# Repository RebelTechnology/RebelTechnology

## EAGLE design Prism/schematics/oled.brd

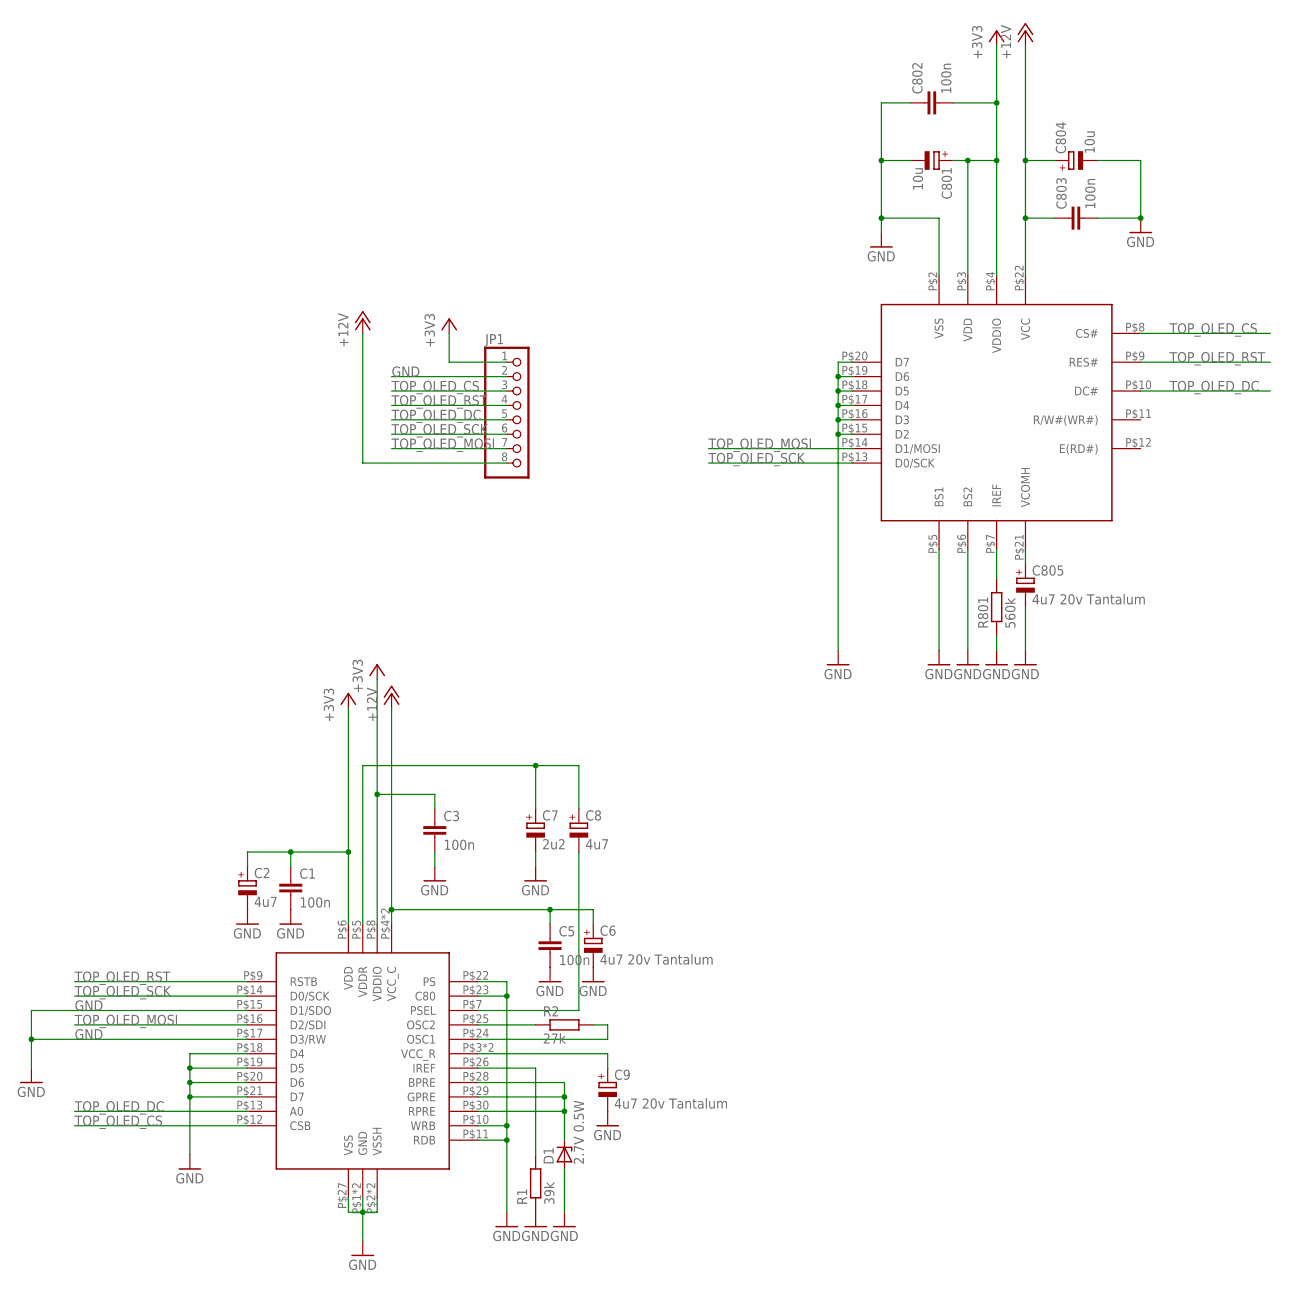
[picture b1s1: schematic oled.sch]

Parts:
C1, C3, C5, C802, C803: 100n; C0603
C2, C8: 4u7; CPOL-5
C6, C9, C805: 4u7 20v Tantalum; CT3216
C7: 2u2; CPOL-5
C801, C804: 10u; CPOL-5
D1: 2.7V 0.5W; SOD80C
JP1: PINHD-1X8; 1X08
OLED: MCOT096064AZ-RGBM
R1: 39k; 0603
R2: 27k; 0603
R801: 560k; 0603
U$1: MCOT096096AY

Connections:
+3V3: C1.1, C2.+, C3.1, C801.+, C802.2, JP1.1, OLED.P$3 (VDD), OLED.P$4 (VDDIO), U$1.P$6 (VDD), U$1.P$8 (VDDIO)
+12V: C5.1, C6.+, C803.1, C804.+, JP1.8, OLED.P$22 (VCC), U$1.P$4 (VCC_C), U$1.P$31 (VCC_C)
GND: C1.2, C2.-, C3.2, C5.2, C6.-, C7.-, C9.-, C801.-, C802.1, C803.2, C804.-, C805.-, D1.A, JP1.2, OLED.P$2 (VSS), OLED.P$5 (BS1), OLED.P$6 (BS2), OLED.P$15 (D2), OLED.P$16 (D3), OLED.P$17 (D4), OLED.P$18 (D5), OLED.P$19 (D6), OLED.P$20 (D7), R1.1, R801.1, U$1.P$1 (GND), U$1.P$2 (VSSH), U$1.P$10 (WRB), U$1.P$11 (RDB), U$1.P$15 (D1/SDO), U$1.P$17 (D3/RW), U$1.P$18 (D4), U$1.P$19 (D5), U$1.P$20 (D6), U$1.P$21 (D7), U$1.P$22 (PS), U$1.P$23 (C80), U$1.P$27 (VSS), U$1.P$33 (VSSH), U$1.P$34 (GND)
unnamed: C9.+, U$1.P$3 (VCC_R), U$1.P$32 (VCC_R)
unnamed: C7.+, C8.+, U$1.P$5 (VDDR)
unnamed: C805.+, OLED.P$21 (VCOMH)
unnamed: C8.-, U$1.P$7 (PSEL)
unnamed: OLED.P$7 (IREF), R801.2
unnamed: D1.C, U$1.P$28 (BPRE), U$1.P$29 (GPRE), U$1.P$30 (RPRE)
unnamed: R2.1, U$1.P$25 (OSC2)
unnamed: R2.2, U$1.P$24 (OSC1)
unnamed: R1.2, U$1.P$26 (IREF)
TOP_OLED_CS: JP1.3, OLED.P$8 (CS#), U$1.P$12 (CSB)
TOP_OLED_DC: JP1.5, OLED.P$10 (DC#), U$1.P$13 (A0)
TOP_OLED_MOSI: JP1.7, OLED.P$14 (D1/MOSI), U$1.P$16 (D2/SDI)
TOP_OLED_RST: JP1.4, OLED.P$9 (RES#), U$1.P$9 (RSTB)
TOP_OLED_SCK: JP1.6, OLED.P$13 (D0/SCK), U$1.P$14 (D0/SCK)

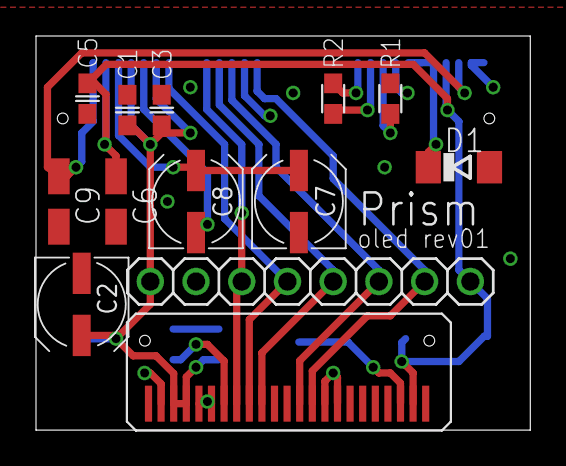
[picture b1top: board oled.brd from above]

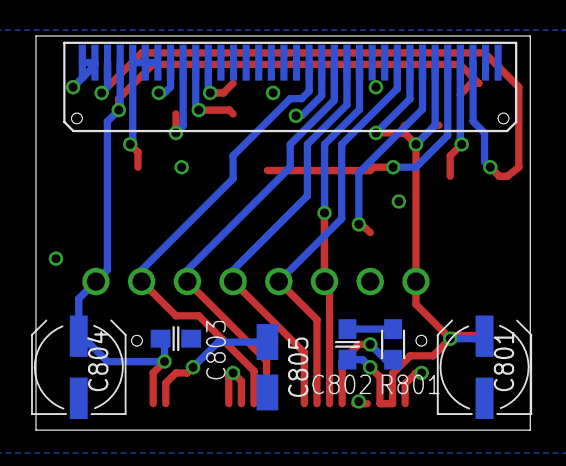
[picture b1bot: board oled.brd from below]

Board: 2 copper layers, 27.5 x 21.9 mm, 20 parts (7 on the bottom side), 17 nets.

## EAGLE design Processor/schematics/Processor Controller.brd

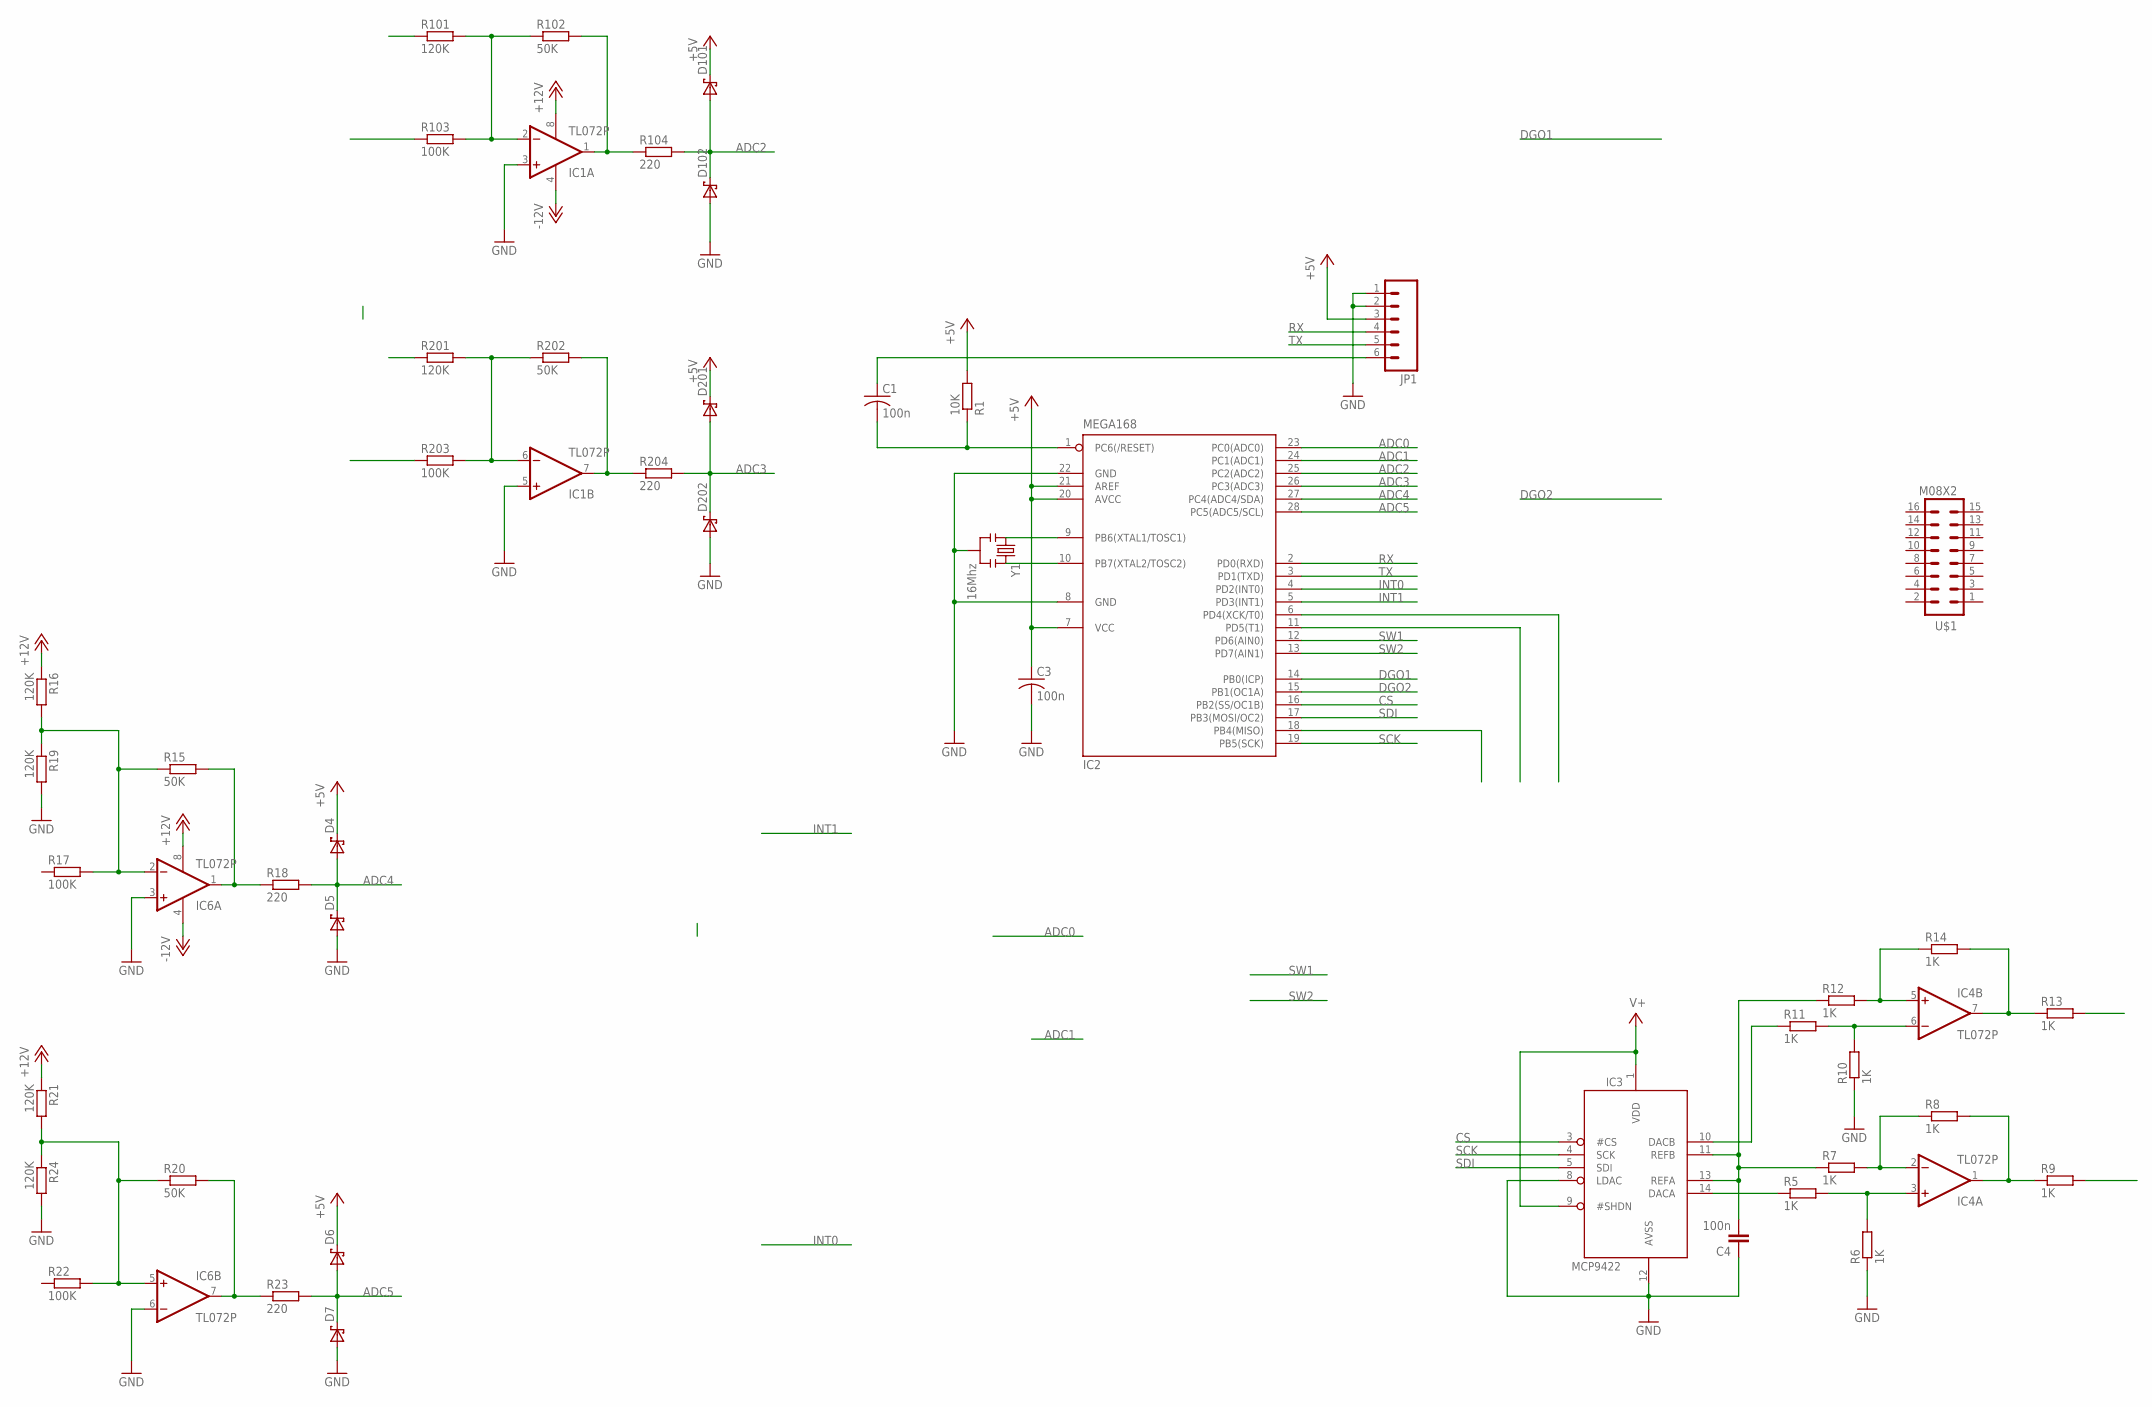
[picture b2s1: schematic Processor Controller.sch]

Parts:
C1, C3: 100n; C050-024X044
C4: 100n; C050-030X075
D4, D5, D6, D7, D101, D102, D201, D202: DS_E2L; E2LINE
IC1, IC4, IC6: TL072P; DIL08
IC2: MEGA168; DIL28-3
IC3: MCP9422; DIL14
JP1: M06SIP; 1X06
R1: 10K; 0204/7
R5, R6, R7, R8, R9, R10, R11, R12, R13, R14: 1K; 0204/7
R15, R20, R102, R202: 50K; 0204/7
R16, R19, R21, R24, R101, R201: 120K; 0204/7
R17, R22, R103, R203: 100K; 0204/7
R18, R23, R104, R204: 220; 0204/7
U$1: M08X2; 2X8
Y1: 16Mhz; RESONATOR-PTH

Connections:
+5V: C3.1, D4.1 (K), D6.1 (K), D101.1 (K), D201.1 (K), IC2.7 (VCC), IC2.20 (AVCC), IC2.21 (AREF), JP1.3, R1.2
+12V: IC1.8 (V+), IC6.8 (V+), R16.1, R21.1
-12V: IC1.4 (V-), IC6.4 (V-)
ADC0: IC2.23 (PC0(ADC0))
ADC1: IC2.24 (PC1(ADC1))
ADC2: D101.2 (A), D102.1 (K), IC2.25 (PC2(ADC2)), R104.2
ADC3: D201.2 (A), D202.1 (K), IC2.26 (PC3(ADC3)), R204.2
ADC4: D4.2 (A), D5.1 (K), IC2.27 (PC4(ADC4/SDA)), R18.2
ADC5: D6.2 (A), D7.1 (K), IC2.28 (PC5(ADC5/SCL)), R23.2
ALTA: IC2.11 (PD5(T1))
CS: IC2.16 (PB2(SS/OC1B)), IC3.3 (#CS)
DGO1: IC2.14 (PB0(ICP))
DGO2: IC2.15 (PB1(OC1A))
GND: C3.2, C4.1, D5.2 (A), D7.2 (A), D102.2 (A), D202.2 (A), IC1.3 (+IN), IC1.5 (+IN), IC2.8 (GND), IC2.22 (GND), IC3.8 (LDAC), IC3.12 (AVSS), IC6.3 (+IN), IC6.6 (-IN), JP1.1, JP1.2, R6.1, R10.1, R19.2, R24.2, Y1.2
INT0: IC2.4 (PD2(INT0))
INT1: IC2.5 (PD3(INT1))
unnamed: IC1.2 (-IN), R101.2, R102.1, R103.2
unnamed: IC1.1 (OUT), R102.2, R104.1
unnamed: IC1.6 (-IN), R201.2, R202.1, R203.2
unnamed: IC1.7 (OUT), R202.2, R204.1
unnamed: C4.2, IC3.11 (REFB), IC3.13 (REFA), R7.1, R12.1
unnamed: IC4.2 (-IN), R7.2, R8.1
unnamed: IC4.3 (+IN), R5.2, R6.2
unnamed: IC3.14 (DACA), R5.1
unnamed: IC4.1 (OUT), R8.2, R9.1
unnamed: IC2.9 (PB6(XTAL1/TOSC1)), Y1.1
unnamed: IC2.10 (PB7(XTAL2/TOSC2)), Y1.3
unnamed: IC6.2 (-IN), R15.1, R16.2, R17.2, R19.1
unnamed: C1.1, JP1.6
unnamed: IC3.10 (DACB), R11.1
unnamed: IC4.6 (-IN), R10.2, R11.2
unnamed: IC4.5 (+IN), R12.2, R14.1
unnamed: C1.2, IC2.1 (PC6(/RESET)), R1.1
unnamed: IC4.7 (OUT), R13.1, R14.2
unnamed: IC6.1 (OUT), R15.2, R18.1
unnamed: IC6.7 (OUT), R20.2, R23.1
unnamed: IC6.5 (+IN), R20.1, R21.2, R22.2, R24.1
RX: IC2.2 (PD0(RXD)), JP1.4
SCK: IC2.19 (PB5(SCK)), IC3.4 (SCK)
SDI: IC2.17 (PB3(MOSI/OC2)), IC3.5 (SDI)
SW1: IC2.12 (PD6(AIN0))
SW2: IC2.13 (PD7(AIN1))
TRIGA: IC2.6 (PD4(XCK/T0))
TX: IC2.3 (PD1(TXD)), JP1.5
V+: IC3.1 (VDD), IC3.9 (#SHDN), IC4.8 (V+)
V-: IC4.4 (V-)

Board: 2 copper layers, 48 parts (0 on the bottom side), 35 nets, no tracks yet.

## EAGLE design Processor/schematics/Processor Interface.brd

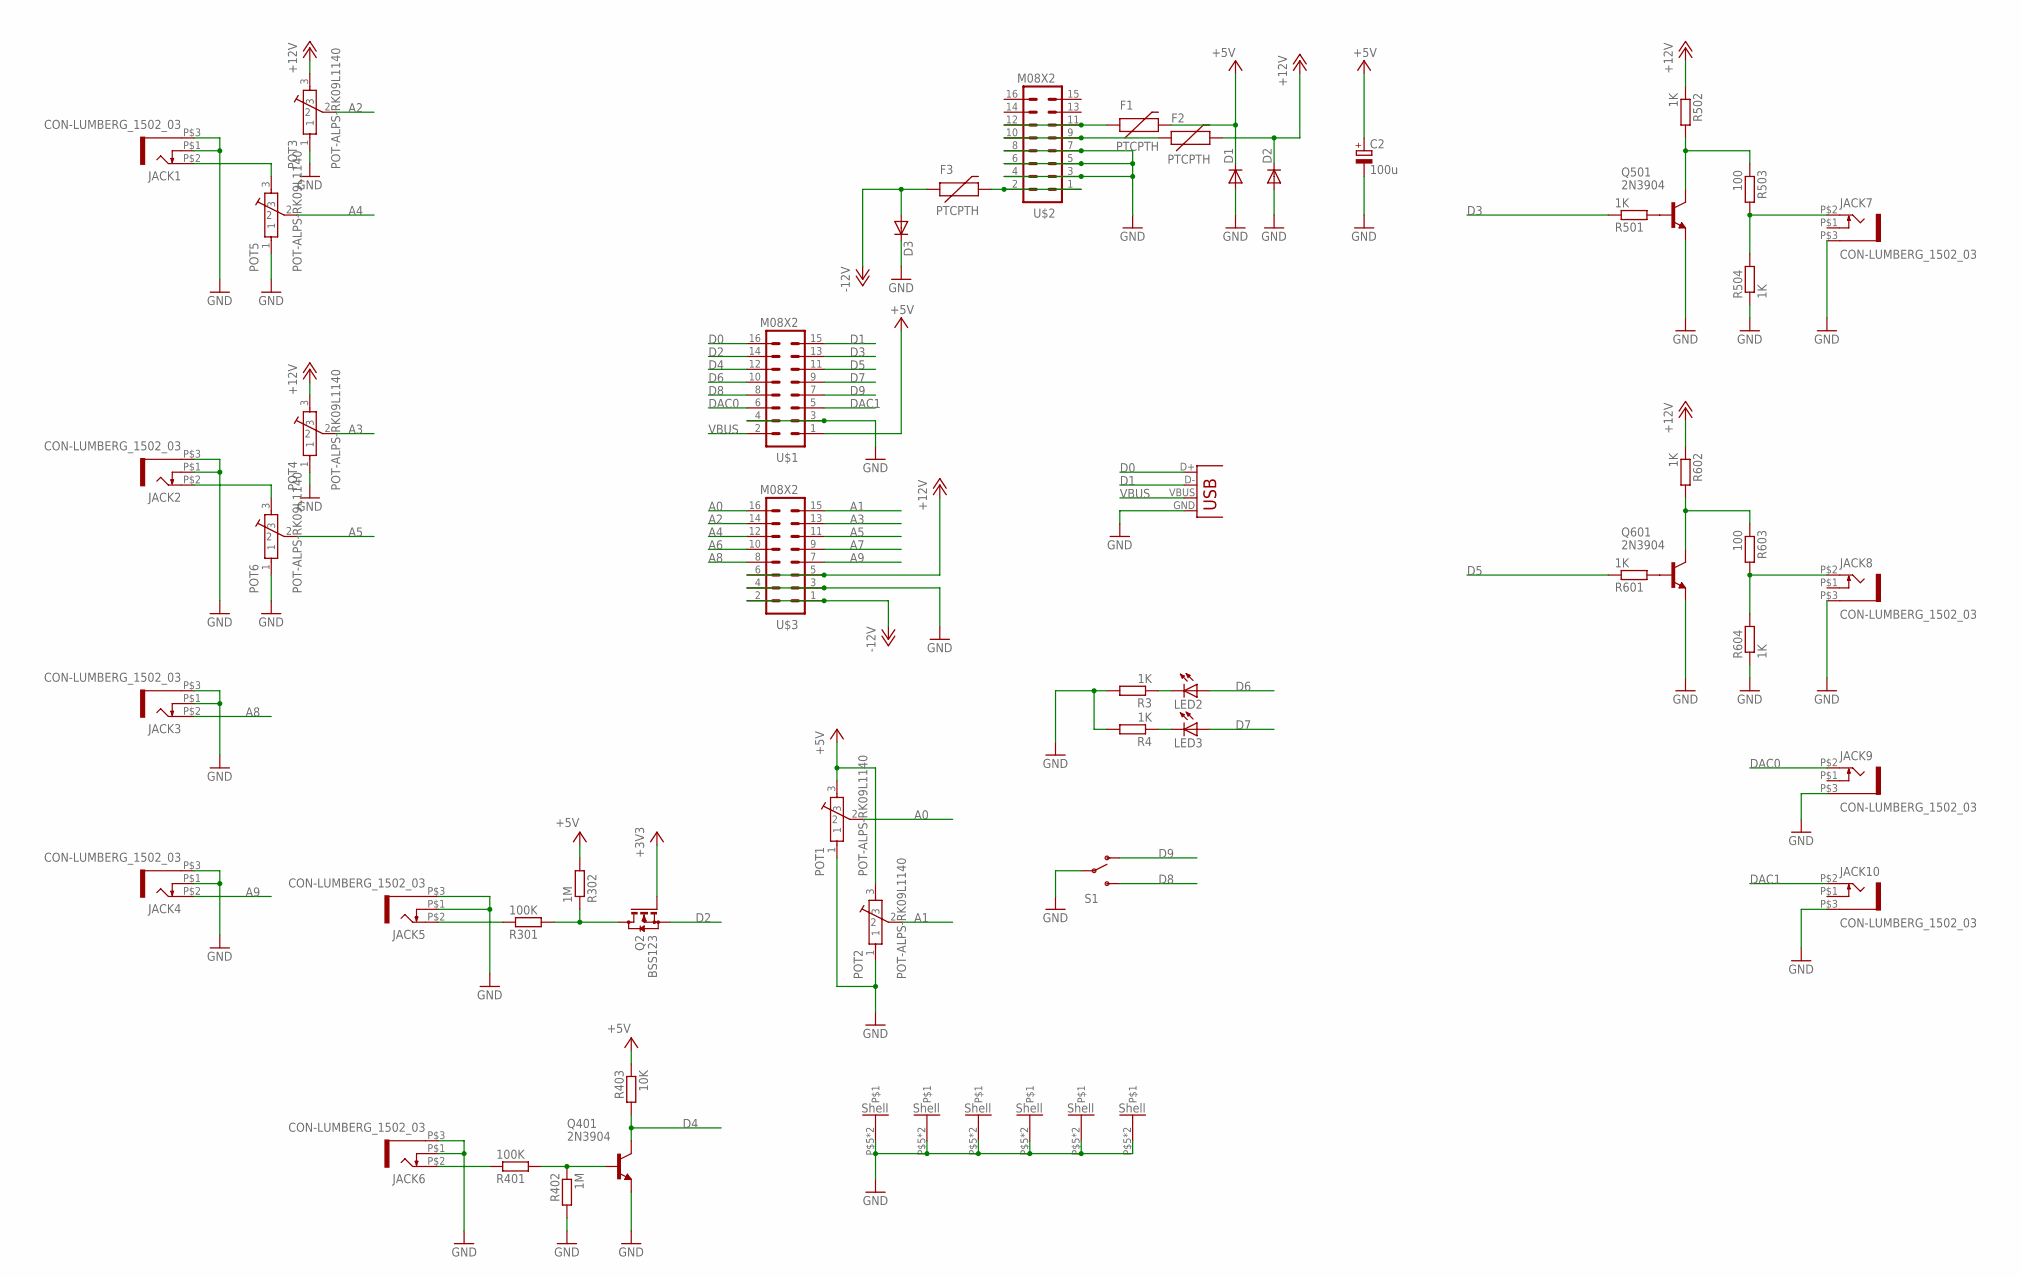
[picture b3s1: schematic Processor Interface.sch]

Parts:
C2: 100u; E5-6
D1, D2, D3: DIODEPTH; DIODE-1N4001
F1, F2, F3: PTCPTH; PTC
JACK1, JACK2, JACK3, JACK4, JACK5, JACK6, JACK7, JACK8, JACK9, JACK10: CON-LUMBERG_1502_03
LED2, LED3: LED3MM
POT1, POT2, POT3, POT4, POT5, POT6: POT-ALPS-RK09L1140
Q2: BSS123; SOT23
Q401, Q501, Q601: 2N3904; TO92
R3, R4, R501, R502, R504, R601, R602, R604: 1K; 0204/7
R301, R401: 100K; 0204/7
R302, R402: 1M; 0204/7
R403: 10K; 0204/7
R503, R603: 100; 0204/7
S1: SWITCH-SPST; SWITCH-SPDT-SALECOM-T8014
U$1, U$2, U$3: M08X2; 2X8
X1: USBPTH-VERTICAL; USB-B-PTH-VERTICAL

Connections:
+3V3: Q2.1 (G)
+5V: C2.+, D1.C, F1.P$2 (2), POT1.3, POT2.3, R302.2, R403.1, U$1.1
+12V: D2.C, F2.P$2 (2), POT3.3, POT4.3, R502.1, R602.1, U$3.5, U$3.6
-12V: D3.A, F3.P$1 (1), U$3.1, U$3.2
A0: POT1.2, U$3.16
A1: POT2.2, U$3.15
A2: POT3.2, U$3.14
A3: POT4.2, U$3.13
A4: POT5.2, U$3.12
A5: POT6.2, U$3.11
A6: U$3.10
A7: U$3.9
A8: JACK3.P$2 (3), U$3.8
A9: JACK4.P$2 (3), U$3.7
D0: U$1.16, X1.D+
D1: U$1.15, X1.D-
D2: Q2.2 (S), U$1.14
D3: R501.1, U$1.13
D4: Q401.1 (C), R403.2, U$1.12
D5: R601.1, U$1.11
D6: LED2.A, U$1.10
D7: LED3.A, U$1.9
D8: S1.3 (S), U$1.8
D9: S1.1 (O), U$1.7
DAC0: JACK9.P$2 (3), U$1.6
DAC1: JACK10.P$2 (3), U$1.5
GND: C2.-, D1.A, D2.A, D3.C, JACK1.P$1 (4), JACK1.P$3 (5), JACK2.P$1 (4), JACK2.P$3 (5), JACK3.P$1 (4), JACK3.P$3 (5), JACK4.P$1 (4), JACK4.P$3 (5), JACK5.P$1 (4), JACK5.P$3 (5), JACK6.P$1 (4), JACK6.P$3 (5), JACK7.P$3 (5), JACK8.P$3 (5), JACK9.P$3 (5), JACK10.P$3 (5), POT1.1, POT1.P$5, POT1.P$6, POT2.1, POT2.P$5, POT2.P$6, POT3.1, POT3.P$5, POT3.P$6, POT4.1, POT4.P$5, POT4.P$6, POT5.1, POT5.P$5, POT5.P$6, POT6.1, POT6.P$5, POT6.P$6, Q401.3 (E), Q501.3 (E), Q601.3 (E), R3.2, R4.2, R402.2, R504.1, R604.1, S1.2, U$1.3, U$1.4, U$2.3, U$2.4, U$2.5, U$2.6, U$2.7, U$2.8, U$3.3, U$3.4, X1.GND
unnamed: JACK1.P$2 (3), POT5.3
unnamed: Q2.3 (D), R301.2, R302.1
unnamed: F3.P$2 (2), U$2.1, U$2.2
unnamed: JACK2.P$2 (3), POT6.3
unnamed: LED2.K (C), R3.1
unnamed: LED3.K (C), R4.1
unnamed: Q601.2 (B), R601.2
unnamed: JACK5.P$2 (3), R301.1
unnamed: JACK8.P$2 (3), R603.2, R604.2
unnamed: Q401.2 (B), R401.2, R402.1
unnamed: Q601.1 (C), R602.2, R603.1
unnamed: Q501.2 (B), R501.2
unnamed: JACK7.P$2 (3), R503.2, R504.2
unnamed: Q501.1 (C), R502.2, R503.1
unnamed: JACK6.P$2 (3), R401.1
unnamed: F1.P$1 (1), U$2.11, U$2.12
unnamed: F2.P$1 (1), U$2.9, U$2.10
VBUS: U$1.2, X1.VBUS

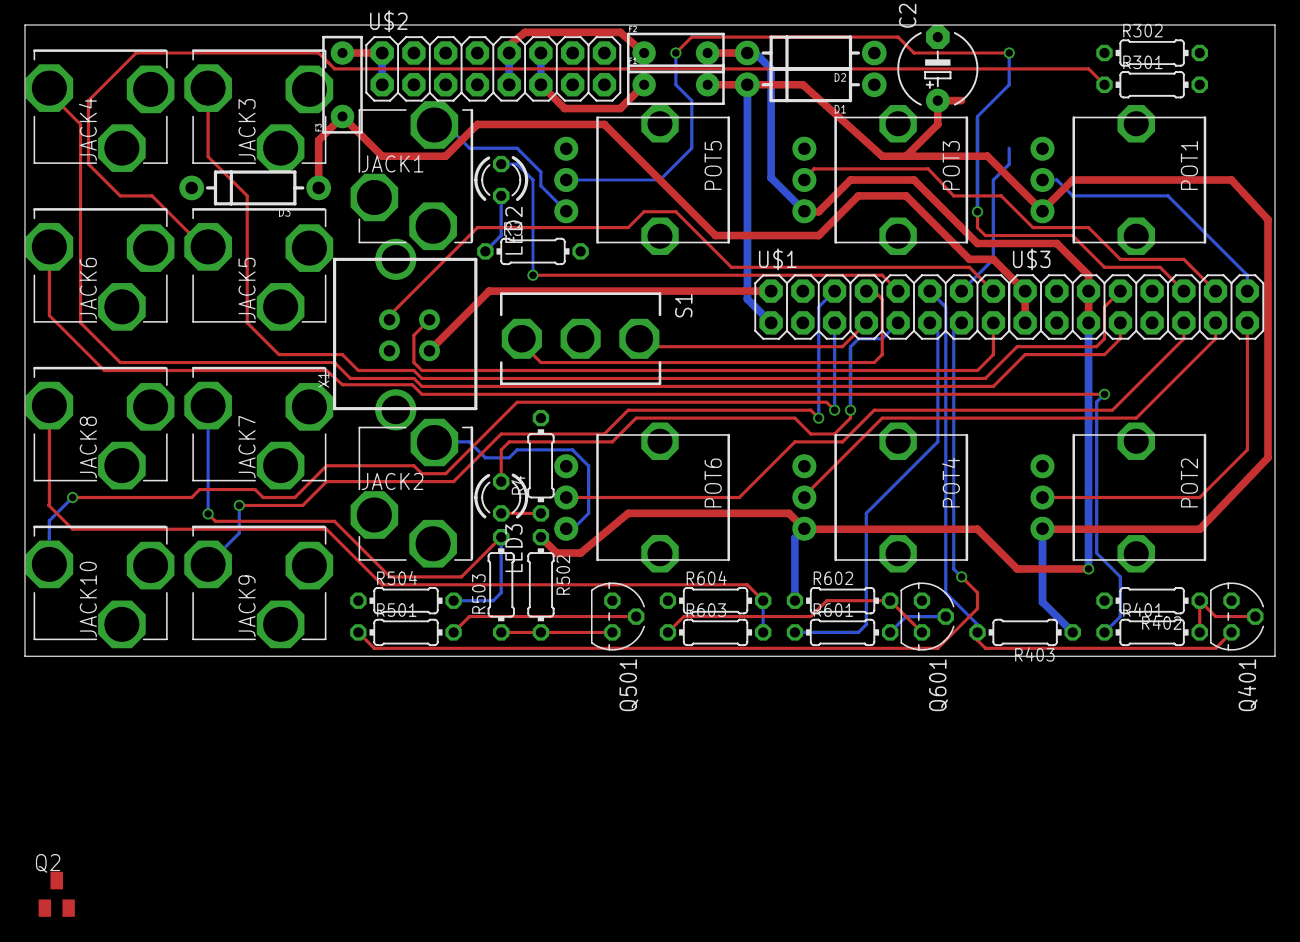
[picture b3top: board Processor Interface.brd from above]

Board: 2 copper layers, 100.0 x 50.5 mm, 49 parts (0 on the bottom side), 42 nets.

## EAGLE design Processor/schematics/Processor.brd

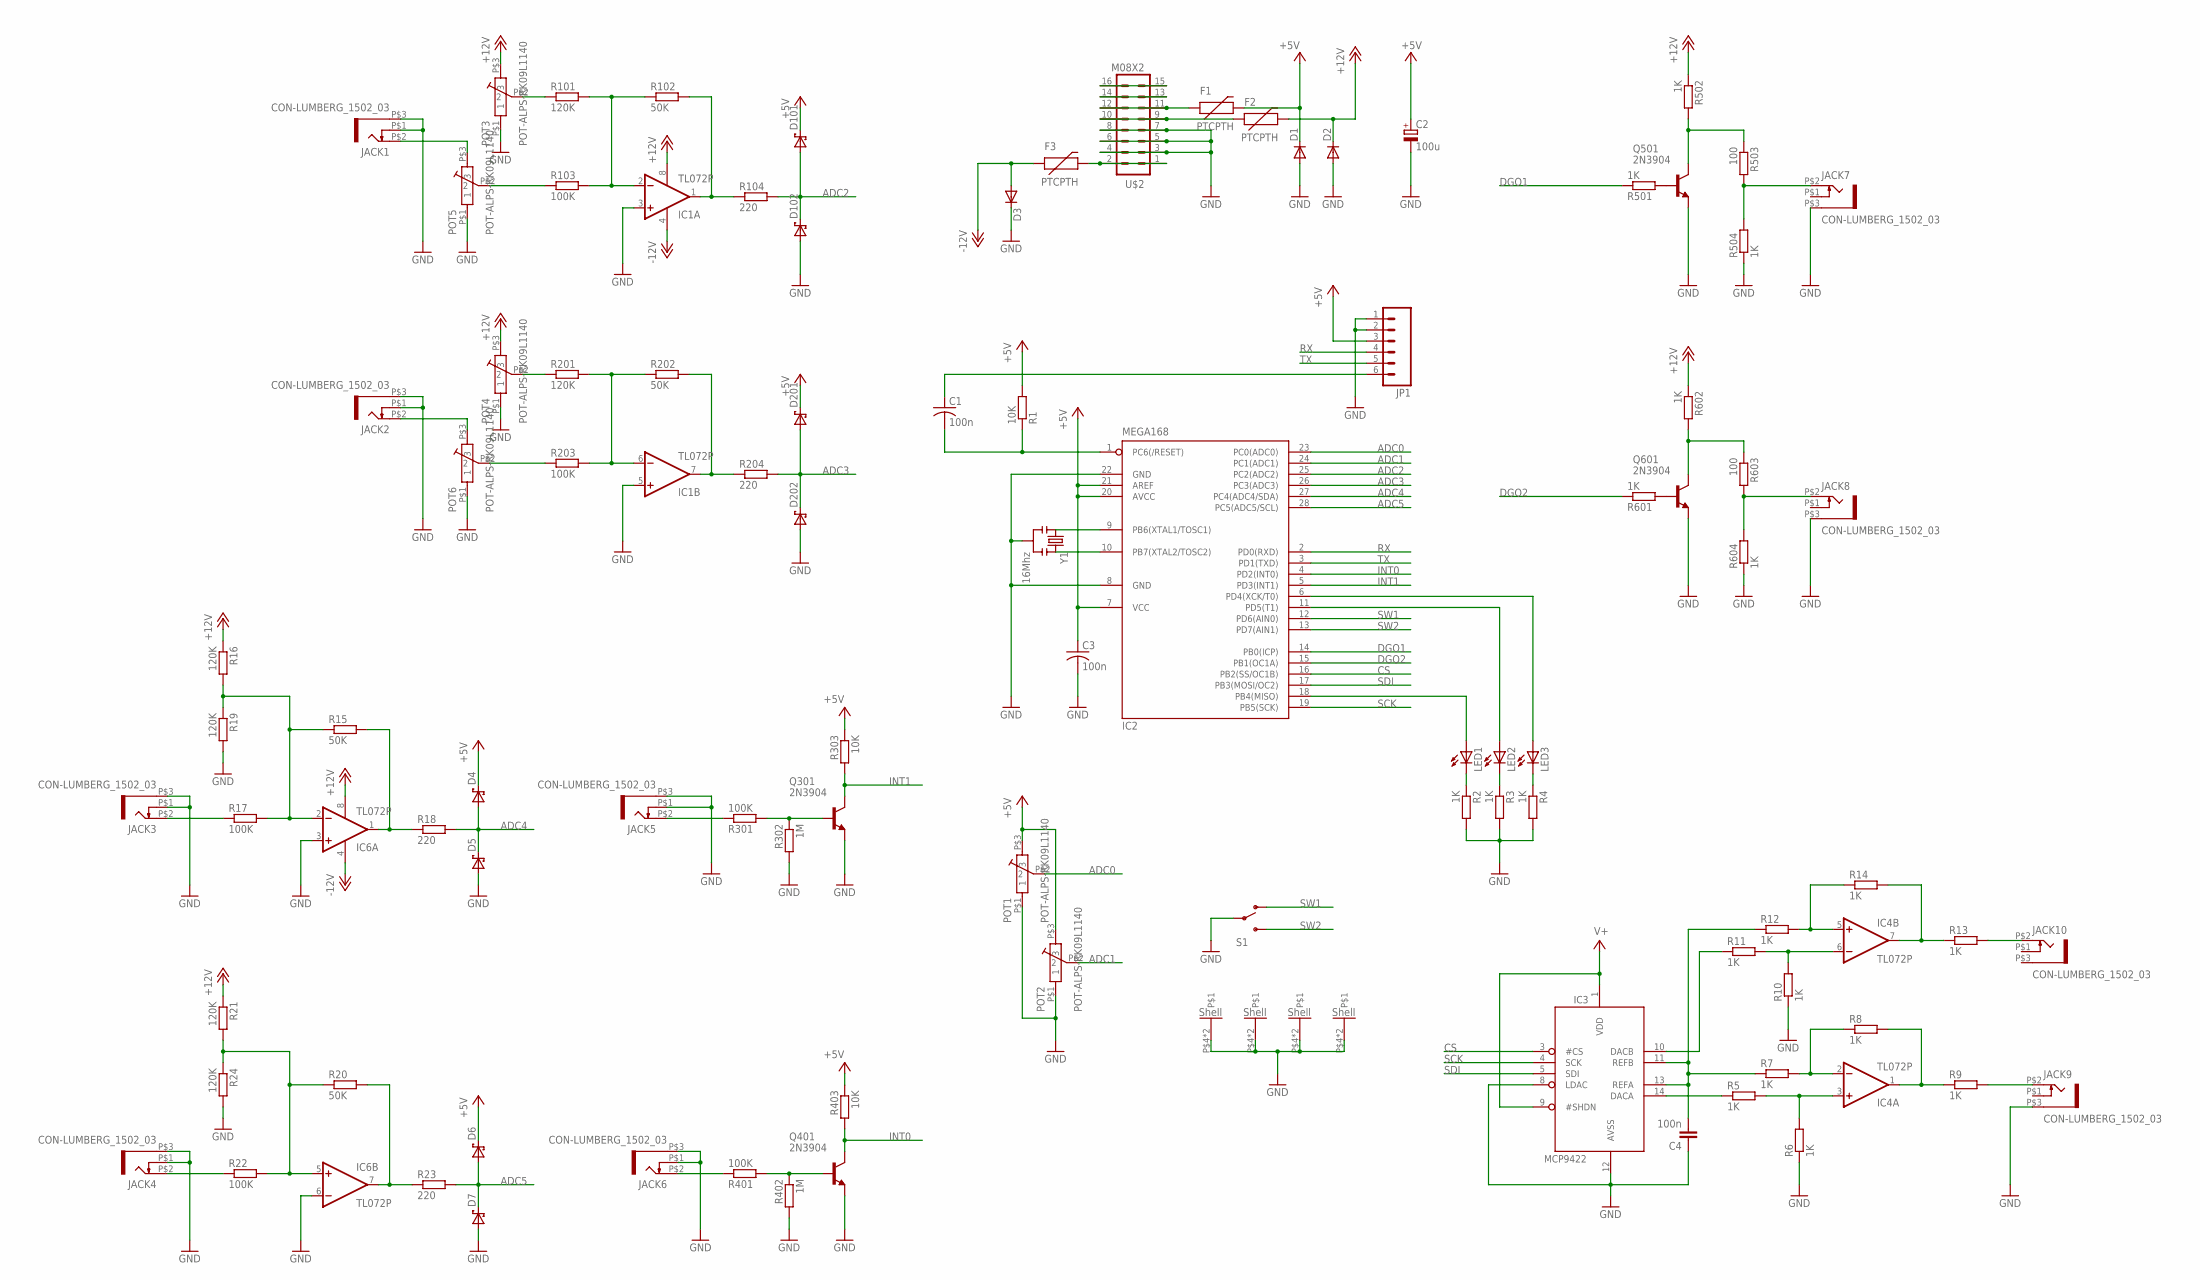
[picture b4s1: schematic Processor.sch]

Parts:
C1, C3: 100n; C050-024X044
C2: 100u; E5-6
C4: 100n; C050-030X075
D1, D2, D3: DIODEPTH; DIODE-1N4001
D4, D5, D6, D7, D101, D102, D201, D202: DS_E2L; E2LINE
F1, F2, F3: PTCPTH; PTC
IC1, IC4, IC6: TL072P; DIL08
IC2: MEGA168; DIL28-3
IC3: MCP9422; DIL14
JACK1, JACK2, JACK3, JACK4, JACK5, JACK6, JACK7, JACK8, JACK9, JACK10: CON-LUMBERG_1502_03
JP1: M06SIP; 1X06
LED1, LED2, LED3: LED3MM
POT1, POT2, POT3, POT4, POT5, POT6: POT-ALPS-RK09L1140
Q301, Q401, Q501, Q601: 2N3904; TO92
R1, R303, R403: 10K; 0204/7
R2, R3, R4, R5, R6, R7, R8, R9, R10, R11, R12, R13, R14, R501, R502, R504, R601, R602, R604: 1K; 0204/7
R15, R20, R102, R202: 50K; 0204/7
R16, R19, R21, R24, R101, R201: 120K; 0204/7
R17, R22, R103, R203, R301, R401: 100K; 0204/7
R18, R23, R104, R204: 220; 0204/7
R302, R402: 1M; 0204/7
R503, R603: 100; 0204/7
S1: SWITCH-SPST; SWITCH-SPDT-SALECOM-T8014
U$2: M08X2; 2X8
Y1: 16Mhz; RESONATOR-PTH

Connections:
+5V: C2.+, C3.1, D1.C, D4.1 (K), D6.1 (K), D101.1 (K), D201.1 (K), F1.P$2 (2), IC2.7 (VCC), IC2.20 (AVCC), IC2.21 (AREF), JP1.3, POT1.P$3 (3), POT2.P$3 (3), R1.2, R303.1, R403.1
+12V: D2.C, F2.P$2 (2), IC1.8 (V+), IC6.8 (V+), POT3.P$3 (3), POT4.P$3 (3), R16.1, R21.1, R502.1, R602.1
-12V: D3.A, F3.P$1 (1), IC1.4 (V-), IC6.4 (V-)
ADC0: IC2.23 (PC0(ADC0)), POT1.P$2 (2)
ADC1: IC2.24 (PC1(ADC1)), POT2.P$2 (2)
ADC2: D101.2 (A), D102.1 (K), IC2.25 (PC2(ADC2)), R104.2
ADC3: D201.2 (A), D202.1 (K), IC2.26 (PC3(ADC3)), R204.2
ADC4: D4.2 (A), D5.1 (K), IC2.27 (PC4(ADC4/SDA)), R18.2
ADC5: D6.2 (A), D7.1 (K), IC2.28 (PC5(ADC5/SCL)), R23.2
ALTA: IC2.11 (PD5(T1)), LED2.A
CS: IC2.16 (PB2(SS/OC1B)), IC3.3 (#CS)
DGO1: IC2.14 (PB0(ICP)), R501.1
DGO2: IC2.15 (PB1(OC1A)), R601.1
GND: C2.-, C3.2, C4.1, D1.A, D2.A, D3.C, D5.2 (A), D7.2 (A), D102.2 (A), D202.2 (A), IC1.3 (+IN), IC1.5 (+IN), IC2.8 (GND), IC2.22 (GND), IC3.8 (LDAC), IC3.12 (AVSS), IC6.3 (+IN), IC6.6 (-IN), JACK1.P$1 (4), JACK1.P$3 (5), JACK2.P$1 (4), JACK2.P$3 (5), JACK3.P$1 (4), JACK3.P$3 (5), JACK4.P$1 (4), JACK4.P$3 (5), JACK5.P$1 (4), JACK5.P$3 (5), JACK6.P$1 (4), JACK6.P$3 (5), JACK7.P$3 (5), JACK8.P$3 (5), JACK9.P$3 (5), JP1.1, JP1.2, POT1.P$1 (1), POT2.P$1 (1), POT3.P$1 (1), POT3.P$4, POT3.P$6, POT4.P$1 (1), POT4.P$4, POT4.P$6, POT5.P$1 (1), POT5.P$4, POT5.P$6, POT6.P$1 (1), POT6.P$4, POT6.P$6, Q301.3 (E), Q401.3 (E), Q501.3 (E), Q601.3 (E), R2.2, R3.2, R4.2, R6.1, R10.1, R19.2, R24.2, R302.2, R402.2, R504.1, R604.1, S1.2, U$2.3, U$2.4, U$2.5, U$2.6, U$2.7, U$2.8, Y1.2
INT0: IC2.4 (PD2(INT0)), Q401.1 (C), R403.2
INT1: IC2.5 (PD3(INT1)), Q301.1 (C), R303.2
unnamed: JACK1.P$2 (3), POT5.P$3 (3)
unnamed: IC1.2 (-IN), R101.2, R102.1, R103.2
unnamed: POT3.P$2 (2), R101.1
unnamed: IC1.1 (OUT), R102.2, R104.1
unnamed: POT5.P$2 (2), R103.1
unnamed: F3.P$2 (2), U$2.1, U$2.2
unnamed: IC1.6 (-IN), R201.2, R202.1, R203.2
unnamed: POT4.P$2 (2), R201.1
unnamed: IC1.7 (OUT), R202.2, R204.1
unnamed: POT6.P$2 (2), R203.1
unnamed: C4.2, IC3.11 (REFB), IC3.13 (REFA), R7.1, R12.1
unnamed: JACK2.P$2 (3), POT6.P$3 (3)
unnamed: IC4.2 (-IN), R7.2, R8.1
unnamed: IC4.3 (+IN), R5.2, R6.2
unnamed: IC3.14 (DACA), R5.1
unnamed: IC4.1 (OUT), R8.2, R9.1
unnamed: JACK9.P$2 (3), R9.2
unnamed: IC2.18 (PB4(MISO)), LED1.A
unnamed: IC2.9 (PB6(XTAL1/TOSC1)), Y1.1
unnamed: IC2.10 (PB7(XTAL2/TOSC2)), Y1.3
unnamed: IC6.2 (-IN), R15.1, R16.2, R17.2, R19.1
unnamed: LED1.K (C), R2.1
unnamed: LED2.K (C), R3.1
unnamed: LED3.K (C), R4.1
unnamed: Q601.2 (B), R601.2
unnamed: Q301.2 (B), R301.2, R302.1
unnamed: JACK5.P$2 (3), R301.1
unnamed: C1.1, JP1.6
unnamed: JACK8.P$2 (3), R603.2, R604.2
unnamed: Q401.2 (B), R401.2, R402.1
unnamed: Q601.1 (C), R602.2, R603.1
unnamed: Q501.2 (B), R501.2
unnamed: IC3.10 (DACB), R11.1
unnamed: IC4.6 (-IN), R10.2, R11.2
unnamed: JACK7.P$2 (3), R503.2, R504.2
unnamed: Q501.1 (C), R502.2, R503.1
unnamed: IC4.5 (+IN), R12.2, R14.1
unnamed: C1.2, IC2.1 (PC6(/RESET)), R1.1
unnamed: JACK6.P$2 (3), R401.1
unnamed: IC4.7 (OUT), R13.1, R14.2
unnamed: JACK10.P$2 (3), R13.2
unnamed: U$2.13, U$2.14
unnamed: F1.P$1 (1), U$2.11, U$2.12
unnamed: F2.P$1 (1), U$2.9, U$2.10
unnamed: IC6.1 (OUT), R15.2, R18.1
unnamed: JACK3.P$2 (3), R17.1
unnamed: IC6.7 (OUT), R20.2, R23.1
unnamed: JACK4.P$2 (3), R22.1
unnamed: IC6.5 (+IN), R20.1, R21.2, R22.2, R24.1
PWR_BUS: U$2.15, U$2.16
RX: IC2.2 (PD0(RXD)), JP1.4
SCK: IC2.19 (PB5(SCK)), IC3.4 (SCK)
SDI: IC2.17 (PB3(MOSI/OC2)), IC3.5 (SDI)
SW1: IC2.12 (PD6(AIN0)), S1.1 (O)
SW2: IC2.13 (PD7(AIN1)), S1.3 (S)
TRIGA: IC2.6 (PD4(XCK/T0)), LED3.A
TX: IC2.3 (PD1(TXD)), JP1.5
V+: IC3.1 (VDD), IC3.9 (#SHDN), IC4.8 (V+)
V-: IC4.4 (V-)

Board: 2 copper layers, 96 parts (0 on the bottom side), 74 nets, no tracks yet.

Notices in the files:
parts and their libraries:
SparkFun: Licensing: CC v3.0 Share-Alike You are welcome to use this library for commercial purposes.
SparkFun-Aesthetics: Licensing: Creative Commons ShareAlike 4.0 International - https://creativecommons.org/licenses/by-sa/4.0
